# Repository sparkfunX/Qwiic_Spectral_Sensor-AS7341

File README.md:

# Qwiic_IR_Thermometer_MLX90614

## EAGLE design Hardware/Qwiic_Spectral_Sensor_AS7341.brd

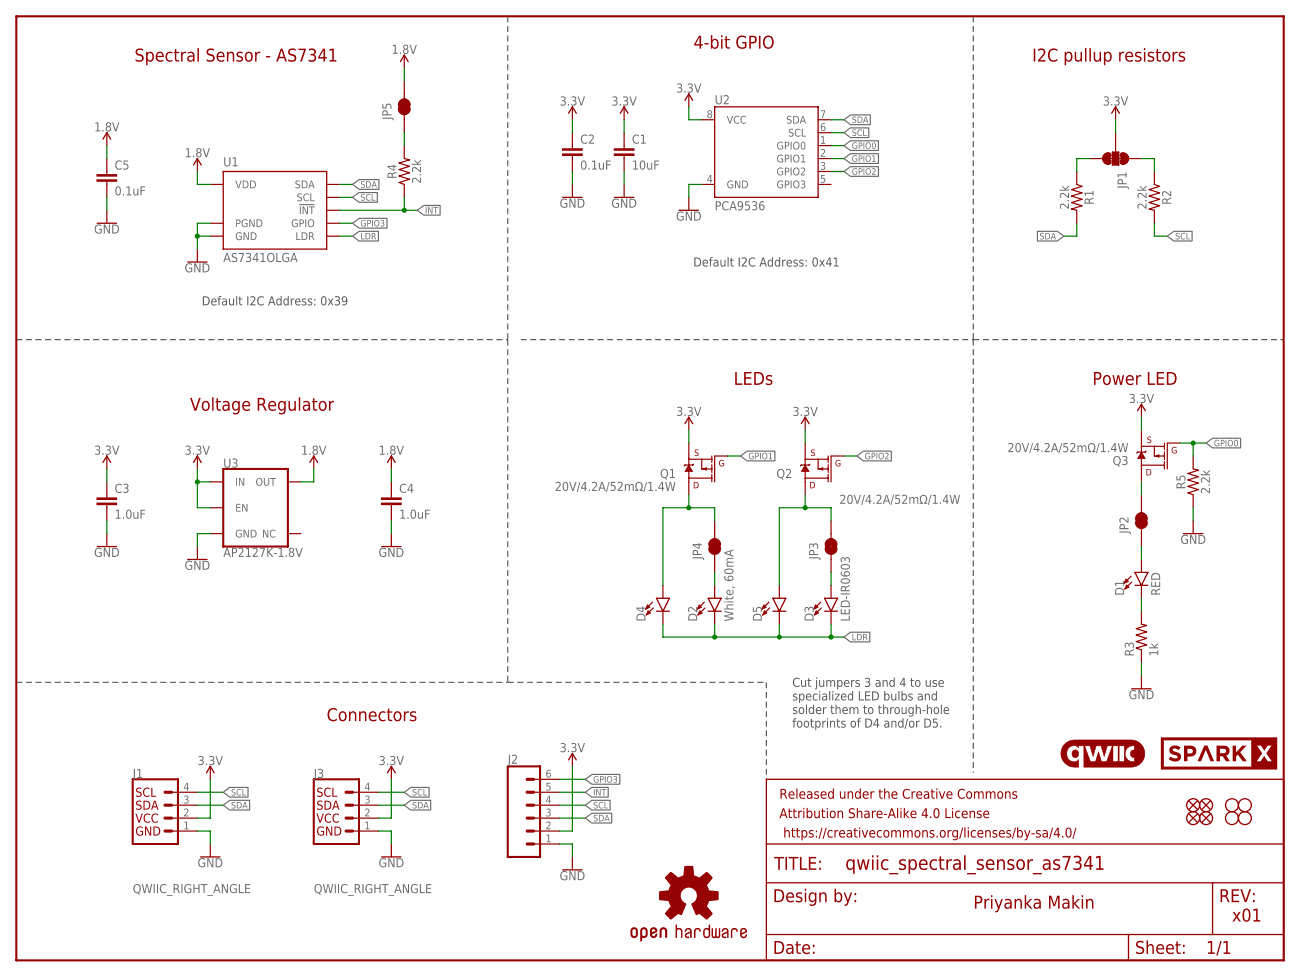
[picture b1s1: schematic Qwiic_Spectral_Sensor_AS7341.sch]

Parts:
C1: 10uF; 0603
C2, C5: 0.1uF; 0603
C3, C4: 1.0uF; 0603
D1: RED; LED-0603
D2: White, 60mA; SUPER_BRIGHT_SMD_LED_3014
D3: LED-IR0603; LED-0603
D4, D5: LED-3MM-NO_SILK; LED_3MM-NS
FD1, FD2, FD3, FD4: FIDUCIAL1X2; FIDUCIAL-1X2
FRAME1: FRAME-LETTER; CREATIVE_COMMONS
H1, H2, H3, H4: STAND-OFF
J1, J3: QWIIC_RIGHT_ANGLE; JST04_1MM_RA
J2: CONN_06NO_SILK_FEMALE_PTH; 1X06_NO_SILK
JP1: JUMPER-SMT_3_2-NC_TRACE_SILK; SMT-JUMPER_3_2-NC_TRACE_SILK
JP2, JP3, JP4, JP5: JUMPER-SMT_2_NC_TRACE_SILK; SMT-JUMPER_2_NC_TRACE_SILK
LOGO1: QWIIC_LOGO_6MM; QWIIC_6MM
Q1, Q2, Q3: 20V/4.2A/52mΩ/1.4W; SOT23-3
R1, R2, R4, R5: 2.2k; 0603
R3: 1k; 0603
U1: AS7341OLGA; OLGA8
U2: PCA9536; MSOP8
U3: AP2127K-1.8V; SOT23-5
U$1: OSHW-LOGOS; OSHW-LOGO-S
U$31: SPARKX-LOGO3; SPARKX-SMALL

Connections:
1.8V: C4.1, C5.1, JP5.2, U1.1 (VDD), U3.5 (OUT)
3.3V: C1.1, C2.1, C3.1, J1.2, J2.2, J3.2, JP1.2, Q1.2 (S), Q2.2 (S), Q3.2 (S), U2.8 (VCC), U3.1 (IN), U3.3 (EN)
!INT!: J2.5, R4.1, U1.7 (!INT!)
GND: C1.2, C2.2, C3.2, C4.2, C5.2, J1.1, J2.1, J3.1, R3.1, R5.1, U1.3 (GND), U1.5 (PGND), U2.4 (GND), U3.2 (GND)
GPIO0: Q3.1 (G), R5.2, U2.1 (GPIO0)
GPIO1: Q1.1 (G), U2.2 (GPIO1)
GPIO2: Q2.1 (G), U2.3 (GPIO2)
GPIO3: J2.6, U1.6 (GPIO)
LDR: D2.C, D3.C, D4.K (C), D5.K (C), U1.4 (LDR)
unnamed: JP1.3, R1.1
unnamed: D1.C, R3.2
unnamed: JP1.1, R2.1
unnamed: D1.A, JP2.1
unnamed: D2.A, JP4.1
unnamed: JP2.2, Q3.3 (D)
unnamed: D3.A, JP3.1
unnamed: D4.A, JP4.2, Q1.3 (D)
unnamed: D5.A, JP3.2, Q2.3 (D)
unnamed: JP5.1, R4.2
SCL: J1.4, J2.4, J3.4, R2.2, U1.2 (SCL), U2.6 (SCL)
SDA: J1.3, J2.3, J3.3, R1.2, U1.8 (SDA), U2.7 (SDA)

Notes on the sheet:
x01
Priyanka Makin
Connectors
Spectral Sensor - AS7341
4-bit GPIO
Power LED
Default I2C Address: 0x39
Default I2C Address: 0x41
I2C pullup resistors
Voltage Regulator
LEDs
Cut jumpers 3 and 4 to use specialized LED bulbs and solder them to through-hole footprints of D4 and/or D5.

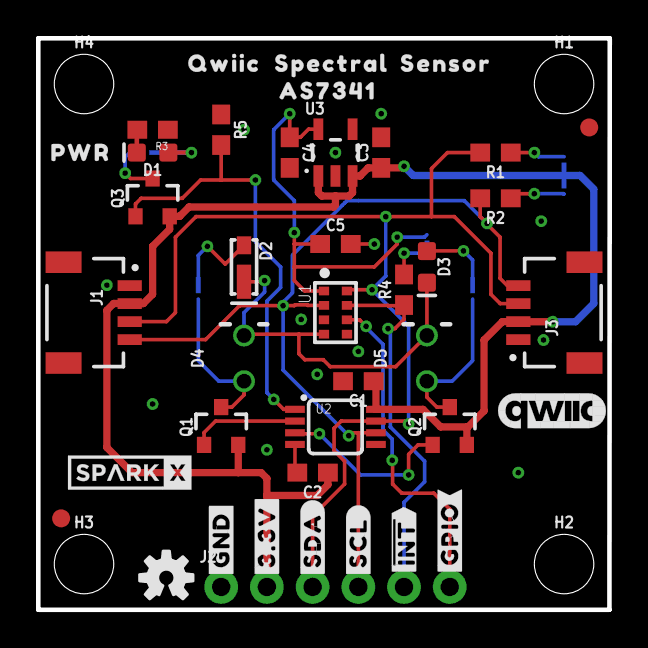
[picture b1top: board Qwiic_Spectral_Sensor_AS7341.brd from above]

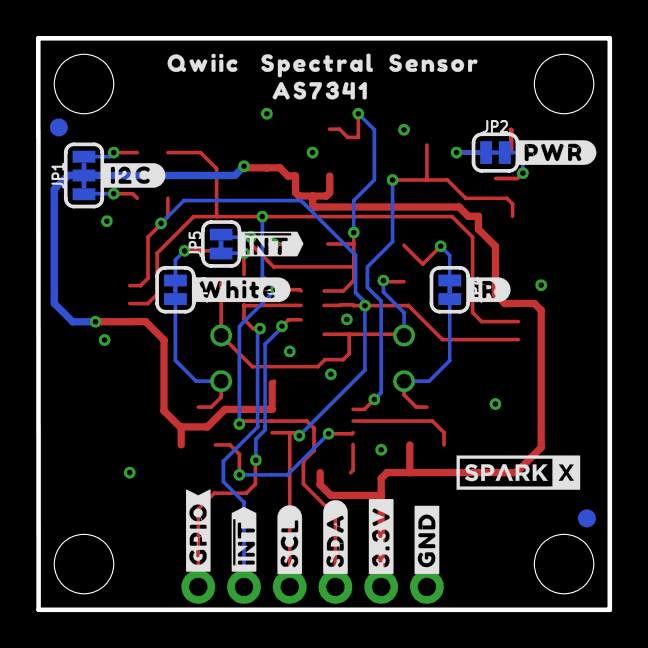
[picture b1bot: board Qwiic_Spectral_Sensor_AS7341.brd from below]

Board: 2 copper layers, 31.8 x 31.8 mm, 68 parts (23 on the bottom side), 21 nets.

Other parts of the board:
U$3, U$4: QWIIC0
U$5, U$8: SPECTRAL0
U$7: SPARKX-SMALL
U$9: #I2C#0
U$10: #PWR#0
U$11, U$21: SENSOR0
U$12: PWR0
U$13, U$14: #GND#0
U$15, U$16: #3#3V#0
U$17, U$18: #SDA#0
U$19, U$20: #SCL#0
U$22, U$23: AS73410
U$24, U$25, U$30: ##INT##0
U$26, U$27: #GPIO#0
U$28: #IR#0
U$29: #WHITE#0

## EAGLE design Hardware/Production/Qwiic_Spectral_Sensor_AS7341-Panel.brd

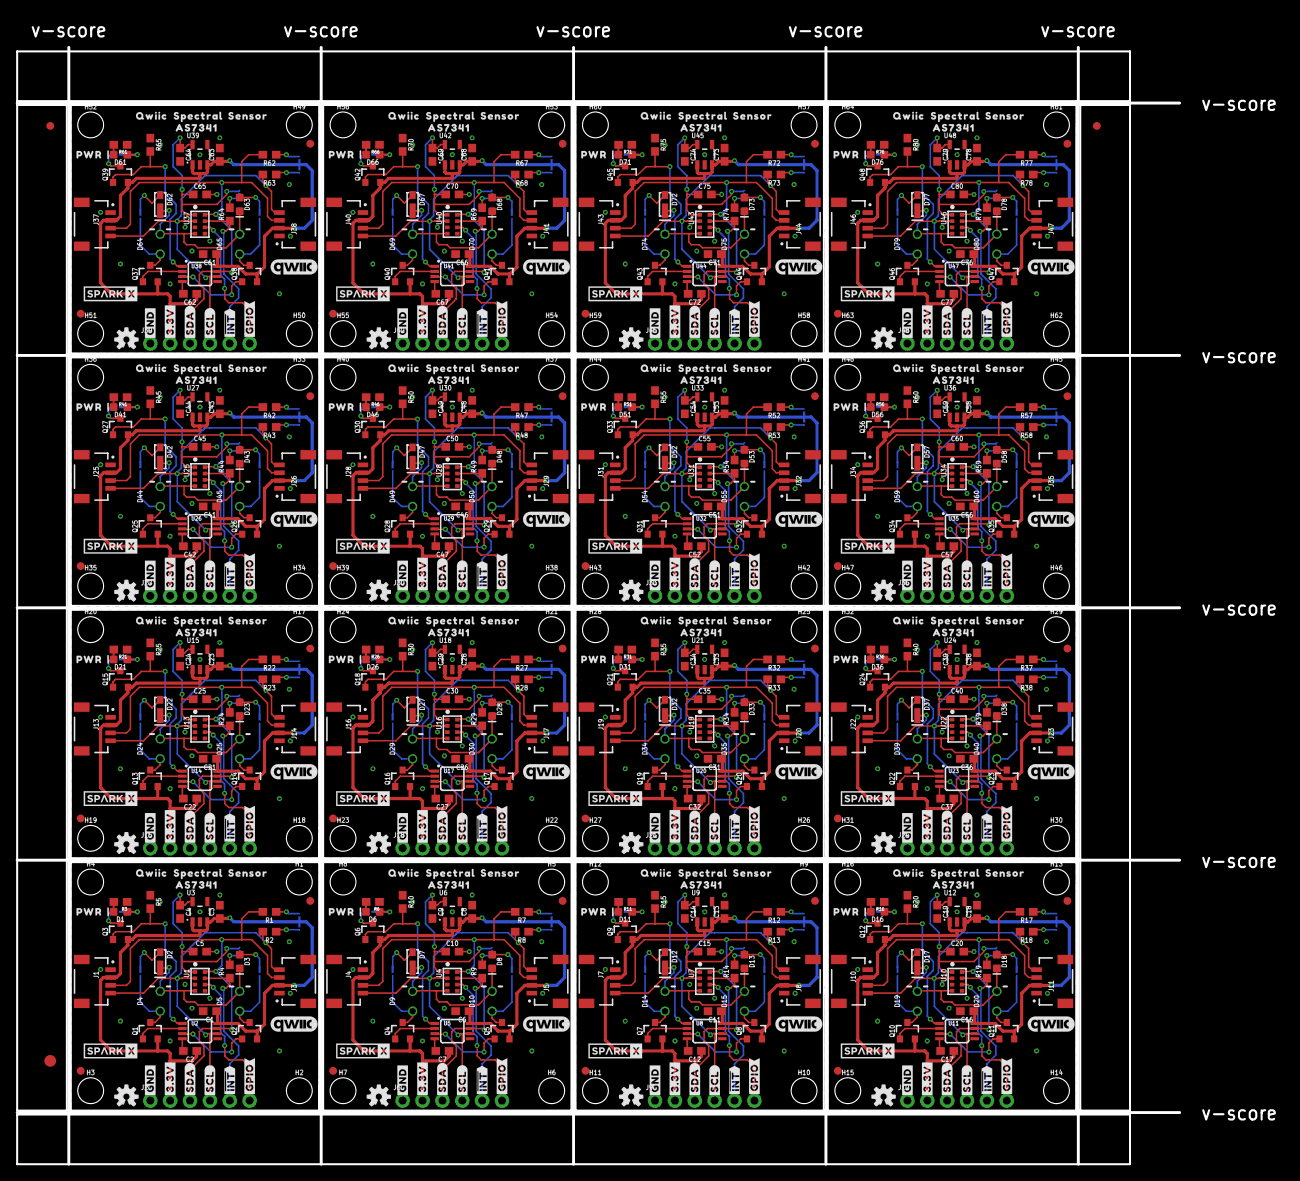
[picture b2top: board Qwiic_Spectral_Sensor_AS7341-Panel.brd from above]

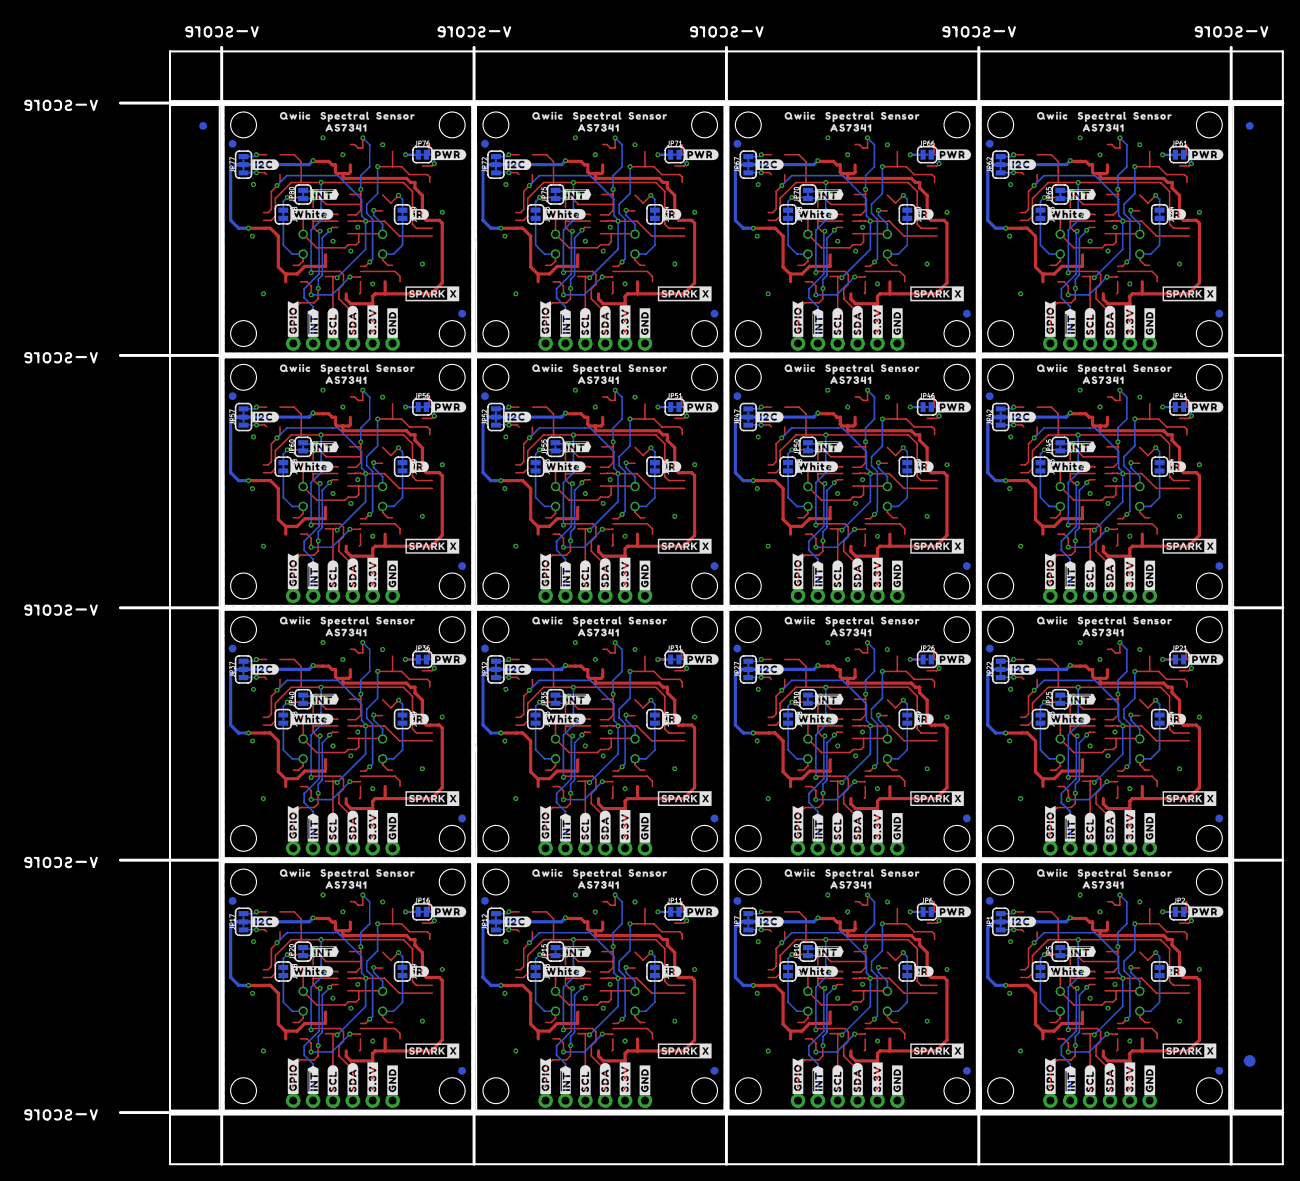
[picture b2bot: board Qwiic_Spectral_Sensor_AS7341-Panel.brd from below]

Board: 2 copper layers, 161.8 x 146.6 mm, 1078 parts (371 on the bottom side), 336 nets.

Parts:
C1, C6, C11, C16, C21, C26, C31, C36, C41, C46, C51, C56, C61, C66, C71, C76: 10uF; 0603
C2, C5, C7, C10, C12, C15, C17, C20, C22, C25, C27, C30, C32, C35, C37, C40, C42, C45, C47, C50, C52, C55, C57, C60, C62, C65, C67, C70, C72, C75, C77, C80: 0.1uF; 0603
C3, C4, C8, C9, C13, C14, C18, C19, C23, C24, C28, C29, C33, C34, C38, C39, C43, C44, C48, C49, C53, C54, C58, C59, C63, C64, C68, C69, C73, C74, C78, C79: 1.0uF; 0603
D1, D6, D11, D16, D21, D26, D31, D36, D41, D46, D51, D56, D61, D66, D71, D76: RED; LED-0603
D2, D7, D12, D17, D22, D27, D32, D37, D42, D47, D52, D57, D62, D67, D72, D77: White, 60mA; SUPER_BRIGHT_SMD_LED_3014
D3, D8, D13, D18, D23, D28, D33, D38, D43, D48, D53, D58, D63, D68, D73, D78: LED-IR0603; LED-0603
D4, D5, D9, D10, D14, D15, D19, D20, D24, D25, D29, D30, D34, D35, D39, D40, D44, D45, D49, D50, D54, D55, D59, D60, D64, D65, D69, D70, D74, D75, D79, D80: LED_3MM-NS
E$1, E$2, E$3, E$4: FIDUCIAL-1X2
E$5, E$6: FIDUCIAL-1.5X3
FD1, FD2, FD3, FD4, FD5, FD6, FD7, FD8, FD9, FD10, FD11, FD12, FD13, FD14, FD15, FD16, FD17, FD18, FD19, FD20, FD21, FD22, FD23, FD24, FD25, FD26, FD27, FD28, FD29, FD30, FD31, FD32, FD33, FD34, FD35, FD36, FD37, FD38, FD39, FD40, FD41, FD42, FD43, FD44, FD45, FD46, FD47, FD48, FD49, FD50, FD51, FD52, FD53, FD54, FD55, FD56, FD57, FD58, FD59, FD60, FD61, FD62, FD63, FD64: FIDUCIAL1X2; FIDUCIAL-1X2
H1, H2, H3, H4, H5, H6, H7, H8, H9, H10, H11, H12, H13, H14, H15, H16, H17, H18, H19, H20, H21, H22, H23, H24, H25, H26, H27, H28, H29, H30, H31, H32, H33, H34, H35, H36, H37, H38, H39, H40, H41, H42, H43, H44, H45, H46, H47, H48, H49, H50, H51, H52, H53, H54, H55, H56, H57, H58, H59, H60, H61, H62, H63, H64: STAND-OFF
J1, J3, J4, J5, J7, J8, J10, J11, J13, J14, J16, J17, J19, J20, J22, J23, J25, J26, J28, J29, J31, J32, J34, J35, J37, J38, J40, J41, J43, J44, J46, J47: QWIIC_RIGHT_ANGLE; JST04_1MM_RA
J2, J6, J9, J12, J15, J18, J21, J24, J27, J30, J33, J36, J39, J42, J45, J48: 1X06_NO_SILK
JP1, JP7, JP12, JP17, JP22, JP27, JP32, JP37, JP42, JP47, JP52, JP57, JP62, JP67, JP72, JP77: JUMPER-SMT_3_2-NC_TRACE_SILK; SMT-JUMPER_3_2-NC_TRACE_SILK
JP2, JP3, JP4, JP5, JP6, JP8, JP9, JP10, JP11, JP13, JP14, JP15, JP16, JP18, JP19, JP20, JP21, JP23, JP24, JP25, JP26, JP28, JP29, JP30, JP31, JP33, JP34, JP35, JP36, JP38, JP39, JP40, JP41, JP43, JP44, JP45, JP46, JP48, JP49, JP50, JP51, JP53, JP54, JP55, JP56, JP58, JP59, JP60, JP61, JP63, JP64, JP65, JP66, JP68, JP69, JP70, JP71, JP73, JP74, JP75, JP76, JP78, JP79, JP80: JUMPER-SMT_2_NC_TRACE_SILK; SMT-JUMPER_2_NC_TRACE_SILK
Q1, Q2, Q3, Q4, Q5, Q6, Q7, Q8, Q9, Q10, Q11, Q12, Q13, Q14, Q15, Q16, Q17, Q18, Q19, Q20, Q21, Q22, Q23, Q24, Q25, Q26, Q27, Q28, Q29, Q30, Q31, Q32, Q33, Q34, Q35, Q36, Q37, Q38, Q39, Q40, Q41, Q42, Q43, Q44, Q45, Q46, Q47, Q48: 20V/4.2A/52mΩ/1.4W; SOT23-3
R1, R2, R4, R5, R7, R8, R9, R10, R12, R13, R14, R15, R17, R18, R19, R20, R22, R23, R24, R25, R27, R28, R29, R30, R32, R33, R34, R35, R37, R38, R39, R40, R42, R43, R44, R45, R47, R48, R49, R50, R52, R53, R54, R55, R57, R58, R59, R60, R62, R63, R64, R65, R67, R68, R69, R70, R72, R73, R74, R75, R77, R78, R79, R80: 2.2k; 0603
R3, R6, R11, R16, R21, R26, R31, R36, R41, R46, R51, R56, R61, R66, R71, R76: 1k; 0603
U1, U4, U7, U10, U13, U16, U19, U22, U25, U28, U31, U34, U37, U40, U43, U46: AS7341OLGA; OLGA8
U2, U5, U8, U11, U14, U17, U20, U23, U26, U29, U32, U35, U38, U41, U44, U47: PCA9536; MSOP8
U3, U6, U9, U12, U15, U18, U21, U24, U27, U30, U33, U36, U39, U42, U45, U48: AP2127K-1.8V; SOT23-5
U$1, U$31, U$61, U$91, U$121, U$151, U$181, U$211, U$241, U$271, U$301, U$331, U$361, U$391, U$421, U$451: OSHW-LOGOS; OSHW-LOGO-S
U$2, U$32, U$62, U$92, U$122, U$152, U$182, U$212, U$242, U$272, U$302, U$332, U$362, U$392, U$422, U$452: QWIIC_6MM
U$3, U$4, U$46, U$47, U$76, U$77, U$106, U$107, U$136, U$137, U$166, U$167, U$196, U$197, U$226, U$227, U$256, U$257, U$286, U$287, U$316, U$317, U$346, U$347, U$376, U$377, U$406, U$407, U$436, U$437, U$466, U$467: QWIIC0
U$5, U$8, U$48, U$49, U$78, U$79, U$108, U$109, U$138, U$139, U$168, U$169, U$198, U$199, U$228, U$229, U$258, U$259, U$288, U$289, U$318, U$319, U$348, U$349, U$378, U$379, U$408, U$409, U$438, U$439, U$468, U$469: SPECTRAL0
U$6, U$7, U$44, U$45, U$74, U$75, U$104, U$105, U$134, U$135, U$164, U$165, U$194, U$195, U$224, U$225, U$254, U$255, U$284, U$285, U$314, U$315, U$344, U$345, U$374, U$375, U$404, U$405, U$434, U$435, U$464, U$465: SPARKX-SMALL
U$9, U$35, U$65, U$95, U$125, U$155, U$185, U$215, U$245, U$275, U$305, U$335, U$365, U$395, U$425, U$455: #I2C#0
U$10, U$34, U$64, U$94, U$124, U$154, U$184, U$214, U$244, U$274, U$304, U$334, U$364, U$394, U$424, U$454: #PWR#0
U$11, U$21, U$50, U$51, U$80, U$81, U$110, U$111, U$140, U$141, U$170, U$171, U$200, U$201, U$230, U$231, U$260, U$261, U$290, U$291, U$320, U$321, U$350, U$351, U$380, U$381, U$410, U$411, U$440, U$441, U$470, U$471: SENSOR0
U$12, U$33, U$63, U$93, U$123, U$153, U$183, U$213, U$243, U$273, U$303, U$333, U$363, U$393, U$423, U$453: PWR0
U$13, U$14, U$36, U$37, U$66, U$67, U$96, U$97, U$126, U$127, U$156, U$157, U$186, U$187, U$216, U$217, U$246, U$247, U$276, U$277, U$306, U$307, U$336, U$337, U$366, U$367, U$396, U$397, U$426, U$427, U$456, U$457: #GND#0
U$15, U$16, U$38, U$39, U$68, U$69, U$98, U$99, U$128, U$129, U$158, U$159, U$188, U$189, U$218, U$219, U$248, U$249, U$278, U$279, U$308, U$309, U$338, U$339, U$368, U$369, U$398, U$399, U$428, U$429, U$458, U$459: #3#3V#0
U$17, U$18, U$40, U$41, U$70, U$71, U$100, U$101, U$130, U$131, U$160, U$161, U$190, U$191, U$220, U$221, U$250, U$251, U$280, U$281, U$310, U$311, U$340, U$341, U$370, U$371, U$400, U$401, U$430, U$431, U$460, U$461: #SDA#0
U$19, U$20, U$42, U$43, U$72, U$73, U$102, U$103, U$132, U$133, U$162, U$163, U$192, U$193, U$222, U$223, U$252, U$253, U$282, U$283, U$312, U$313, U$342, U$343, U$372, U$373, U$402, U$403, U$432, U$433, U$462, U$463: #SCL#0
U$22, U$23, U$52, U$53, U$82, U$83, U$112, U$113, U$142, U$143, U$172, U$173, U$202, U$203, U$232, U$233, U$262, U$263, U$292, U$293, U$322, U$323, U$352, U$353, U$382, U$383, U$412, U$413, U$442, U$443, U$472, U$473: AS73410
U$24, U$25, U$30, U$56, U$57, U$58, U$86, U$87, U$88, U$116, U$117, U$118, U$146, U$147, U$148, U$176, U$177, U$178, U$206, U$207, U$208, U$236, U$237, U$238, U$266, U$267, U$268, U$296, U$297, U$298, U$326, U$327, U$328, U$356, U$357, U$358, U$386, U$387, U$388, U$416, U$417, U$418, U$446, U$447, U$448, U$476, U$477, U$478: ##INT##0
U$26, U$27, U$59, U$60, U$89, U$90, U$119, U$120, U$149, U$150, U$179, U$180, U$209, U$210, U$239, U$240, U$269, U$270, U$299, U$300, U$329, U$330, U$359, U$360, U$389, U$390, U$419, U$420, U$449, U$450, U$479, U$480: #GPIO#0
U$28, U$54, U$84, U$114, U$144, U$174, U$204, U$234, U$264, U$294, U$324, U$354, U$384, U$414, U$444, U$474: #IR#0
U$29, U$55, U$85, U$115, U$145, U$175, U$205, U$235, U$265, U$295, U$325, U$355, U$385, U$415, U$445, U$475: #WHITE#0

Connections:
1.8V: C4.1, C5.1, JP5.2, U1.1, U3.5
1.8V1: C9.1, C10.1, JP10.2, U4.1, U6.5
1.8V2: C14.1, C15.1, JP15.2, U7.1, U9.5
1.8V3: C19.1, C20.1, JP20.2, U10.1, U12.5
1.8V4: C24.1, C25.1, JP25.2, U13.1, U15.5
1.8V5: C29.1, C30.1, JP30.2, U16.1, U18.5
1.8V6: C34.1, C35.1, JP35.2, U19.1, U21.5
1.8V7: C39.1, C40.1, JP40.2, U22.1, U24.5
1.8V8: C44.1, C45.1, JP45.2, U25.1, U27.5
1.8V9: C49.1, C50.1, JP50.2, U28.1, U30.5
1.8V10: C54.1, C55.1, JP55.2, U31.1, U33.5
1.8V11: C59.1, C60.1, JP60.2, U34.1, U36.5
1.8V12: C64.1, C65.1, JP65.2, U37.1, U39.5
1.8V13: C69.1, C70.1, JP70.2, U40.1, U42.5
1.8V14: C74.1, C75.1, JP75.2, U43.1, U45.5
1.8V15: C79.1, C80.1, JP80.2, U46.1, U48.5
3.3V: C1.1, C2.1, C3.1, J1.2, J2.2, J3.2, JP1.2, Q1.2, Q2.2, Q3.2, U2.8, U3.1, U3.3
3.3V1: C6.1, C7.1, C8.1, J4.2, J5.2, J6.2, JP7.2, Q4.2, Q5.2, Q6.2, U5.8, U6.1, U6.3
3.3V2: C11.1, C12.1, C13.1, J7.2, J8.2, J9.2, JP12.2, Q7.2, Q8.2, Q9.2, U8.8, U9.1, U9.3
3.3V3: C16.1, C17.1, C18.1, J10.2, J11.2, J12.2, JP17.2, Q10.2, Q11.2, Q12.2, U11.8, U12.1, U12.3
3.3V4: C21.1, C22.1, C23.1, J13.2, J14.2, J15.2, JP22.2, Q13.2, Q14.2, Q15.2, U14.8, U15.1, U15.3
3.3V5: C26.1, C27.1, C28.1, J16.2, J17.2, J18.2, JP27.2, Q16.2, Q17.2, Q18.2, U17.8, U18.1, U18.3
3.3V6: C31.1, C32.1, C33.1, J19.2, J20.2, J21.2, JP32.2, Q19.2, Q20.2, Q21.2, U20.8, U21.1, U21.3
3.3V7: C36.1, C37.1, C38.1, J22.2, J23.2, J24.2, JP37.2, Q22.2, Q23.2, Q24.2, U23.8, U24.1, U24.3
3.3V8: C41.1, C42.1, C43.1, J25.2, J26.2, J27.2, JP42.2, Q25.2, Q26.2, Q27.2, U26.8, U27.1, U27.3
3.3V9: C46.1, C47.1, C48.1, J28.2, J29.2, J30.2, JP47.2, Q28.2, Q29.2, Q30.2, U29.8, U30.1, U30.3
3.3V10: C51.1, C52.1, C53.1, J31.2, J32.2, J33.2, JP52.2, Q31.2, Q32.2, Q33.2, U32.8, U33.1, U33.3
3.3V11: C56.1, C57.1, C58.1, J34.2, J35.2, J36.2, JP57.2, Q34.2, Q35.2, Q36.2, U35.8, U36.1, U36.3
3.3V12: C61.1, C62.1, C63.1, J37.2, J38.2, J39.2, JP62.2, Q37.2, Q38.2, Q39.2, U38.8, U39.1, U39.3
3.3V13: C66.1, C67.1, C68.1, J40.2, J41.2, J42.2, JP67.2, Q40.2, Q41.2, Q42.2, U41.8, U42.1, U42.3
3.3V14: C71.1, C72.1, C73.1, J43.2, J44.2, J45.2, JP72.2, Q43.2, Q44.2, Q45.2, U44.8, U45.1, U45.3
3.3V15: C76.1, C77.1, C78.1, J46.2, J47.2, J48.2, JP77.2, Q46.2, Q47.2, Q48.2, U47.8, U48.1, U48.3
!INT!: J2.5, R4.1, U1.7
!INT!1: J6.5, R9.1, U4.7
!INT!2: J9.5, R14.1, U7.7
!INT!3: J12.5, R19.1, U10.7
!INT!4: J15.5, R24.1, U13.7
!INT!5: J18.5, R29.1, U16.7
!INT!6: J21.5, R34.1, U19.7
!INT!7: J24.5, R39.1, U22.7
!INT!8: J27.5, R44.1, U25.7
!INT!9: J30.5, R49.1, U28.7
!INT!10: J33.5, R54.1, U31.7
!INT!11: J36.5, R59.1, U34.7
!INT!12: J39.5, R64.1, U37.7
!INT!13: J42.5, R69.1, U40.7
!INT!14: J45.5, R74.1, U43.7
!INT!15: J48.5, R79.1, U46.7
GND: C1.2, C2.2, C3.2, C4.2, C5.2, J1.1, J2.1, J3.1, R3.1, R5.1, U1.3, U1.5, U2.4, U3.2
GND1: C6.2, C7.2, C8.2, C9.2, C10.2, J4.1, J5.1, J6.1, R6.1, R10.1, U4.3, U4.5, U5.4, U6.2
GND2: C11.2, C12.2, C13.2, C14.2, C15.2, J7.1, J8.1, J9.1, R11.1, R15.1, U7.3, U7.5, U8.4, U9.2
GND3: C16.2, C17.2, C18.2, C19.2, C20.2, J10.1, J11.1, J12.1, R16.1, R20.1, U10.3, U10.5, U11.4, U12.2
GND4: C21.2, C22.2, C23.2, C24.2, C25.2, J13.1, J14.1, J15.1, R21.1, R25.1, U13.3, U13.5, U14.4, U15.2
GND5: C26.2, C27.2, C28.2, C29.2, C30.2, J16.1, J17.1, J18.1, R26.1, R30.1, U16.3, U16.5, U17.4, U18.2
GND6: C31.2, C32.2, C33.2, C34.2, C35.2, J19.1, J20.1, J21.1, R31.1, R35.1, U19.3, U19.5, U20.4, U21.2
GND7: C36.2, C37.2, C38.2, C39.2, C40.2, J22.1, J23.1, J24.1, R36.1, R40.1, U22.3, U22.5, U23.4, U24.2
GND8: C41.2, C42.2, C43.2, C44.2, C45.2, J25.1, J26.1, J27.1, R41.1, R45.1, U25.3, U25.5, U26.4, U27.2
GND9: C46.2, C47.2, C48.2, C49.2, C50.2, J28.1, J29.1, J30.1, R46.1, R50.1, U28.3, U28.5, U29.4, U30.2
GND10: C51.2, C52.2, C53.2, C54.2, C55.2, J31.1, J32.1, J33.1, R51.1, R55.1, U31.3, U31.5, U32.4, U33.2
GND11: C56.2, C57.2, C58.2, C59.2, C60.2, J34.1, J35.1, J36.1, R56.1, R60.1, U34.3, U34.5, U35.4, U36.2
GND12: C61.2, C62.2, C63.2, C64.2, C65.2, J37.1, J38.1, J39.1, R61.1, R65.1, U37.3, U37.5, U38.4, U39.2
GND13: C66.2, C67.2, C68.2, C69.2, C70.2, J40.1, J41.1, J42.1, R66.1, R70.1, U40.3, U40.5, U41.4, U42.2
GND14: C71.2, C72.2, C73.2, C74.2, C75.2, J43.1, J44.1, J45.1, R71.1, R75.1, U43.3, U43.5, U44.4, U45.2
GND15: C76.2, C77.2, C78.2, C79.2, C80.2, J46.1, J47.1, J48.1, R76.1, R80.1, U46.3, U46.5, U47.4, U48.2
GPIO0: Q3.1, R5.2, U2.1
GPIO1: Q1.1, U2.2
GPIO2: Q2.1, U2.3
GPIO3: J2.6, U1.6
GPIO4: Q6.1, R10.2, U5.1
GPIO5: Q4.1, U5.2
GPIO6: Q5.1, U5.3
GPIO7: J6.6, U4.6
GPIO8: Q9.1, R15.2, U8.1
GPIO9: Q7.1, U8.2
GPIO10: Q8.1, U8.3
GPIO11: J9.6, U7.6
GPIO12: Q12.1, R20.2, U11.1
GPIO13: Q10.1, U11.2
GPIO14: Q11.1, U11.3
GPIO15: J12.6, U10.6
GPIO16: Q15.1, R25.2, U14.1
GPIO17: Q13.1, U14.2
GPIO18: Q14.1, U14.3
GPIO19: J15.6, U13.6
GPIO20: Q18.1, R30.2, U17.1
GPIO21: Q16.1, U17.2
GPIO22: Q17.1, U17.3
GPIO23: J18.6, U16.6
GPIO24: Q21.1, R35.2, U20.1
GPIO25: Q19.1, U20.2
GPIO26: Q20.1, U20.3
GPIO27: J21.6, U19.6
GPIO28: Q24.1, R40.2, U23.1
GPIO29: Q22.1, U23.2
GPIO30: Q23.1, U23.3
GPIO31: J24.6, U22.6
GPIO32: Q27.1, R45.2, U26.1
GPIO33: Q25.1, U26.2
GPIO34: Q26.1, U26.3
GPIO35: J27.6, U25.6
GPIO36: Q30.1, R50.2, U29.1
GPIO37: Q28.1, U29.2
GPIO38: Q29.1, U29.3
GPIO39: J30.6, U28.6
GPIO40: Q33.1, R55.2, U32.1
GPIO41: Q31.1, U32.2
GPIO42: Q32.1, U32.3
GPIO43: J33.6, U31.6
GPIO44: Q36.1, R60.2, U35.1
GPIO45: Q34.1, U35.2
GPIO46: Q35.1, U35.3
GPIO47: J36.6, U34.6
GPIO48: Q39.1, R65.2, U38.1
GPIO49: Q37.1, U38.2
GPIO50: Q38.1, U38.3
GPIO51: J39.6, U37.6
GPIO52: Q42.1, R70.2, U41.1
GPIO53: Q40.1, U41.2
GPIO54: Q41.1, U41.3
GPIO55: J42.6, U40.6
GPIO56: Q45.1, R75.2, U44.1
GPIO57: Q43.1, U44.2
GPIO58: Q44.1, U44.3
GPIO59: J45.6, U43.6
GPIO60: Q48.1, R80.2, U47.1
GPIO61: Q46.1, U47.2
GPIO62: Q47.1, U47.3
GPIO63: J48.6, U46.6
LDR: D2.C, D3.C, D4.K, D5.K, U1.4
LDR1: D7.C, D8.C, D9.K, D10.K, U4.4
LDR2: D12.C, D13.C, D14.K, D15.K, U7.4
LDR3: D17.C, D18.C, D19.K, D20.K, U10.4
LDR4: D22.C, D23.C, D24.K, D25.K, U13.4
LDR5: D27.C, D28.C, D29.K, D30.K, U16.4
LDR6: D32.C, D33.C, D34.K, D35.K, U19.4
LDR7: D37.C, D38.C, D39.K, D40.K, U22.4
LDR8: D42.C, D43.C, D44.K, D45.K, U25.4
LDR9: D47.C, D48.C, D49.K, D50.K, U28.4
LDR10: D52.C, D53.C, D54.K, D55.K, U31.4
LDR11: D57.C, D58.C, D59.K, D60.K, U34.4
LDR12: D62.C, D63.C, D64.K, D65.K, U37.4
LDR13: D67.C, D68.C, D69.K, D70.K, U40.4
LDR14: D72.C, D73.C, D74.K, D75.K, U43.4
LDR15: D77.C, D78.C, D79.K, D80.K, U46.4
unnamed: JP1.3, R1.1
unnamed: D1.C, R3.2
unnamed: JP1.1, R2.1
unnamed: D1.A, JP2.1
unnamed: D2.A, JP4.1
unnamed: JP2.2, Q3.3
unnamed: D3.A, JP3.1
unnamed: D4.A, JP4.2, Q1.3
unnamed: D5.A, JP3.2, Q2.3
unnamed: JP5.1, R4.2
unnamed: D6.C, R6.2
unnamed: D6.A, JP6.1
unnamed: JP7.3, R7.1
unnamed: JP7.1, R8.1
unnamed: D7.A, JP9.1
unnamed: D8.A, JP8.1
unnamed: D9.A, JP9.2, Q4.3
unnamed: D10.A, JP8.2, Q5.3
unnamed: JP6.2, Q6.3
unnamed: JP10.1, R9.2
unnamed: D11.C, R11.2
unnamed: D11.A, JP11.1
unnamed: JP12.3, R12.1
unnamed: JP12.1, R13.1
unnamed: D12.A, JP14.1
unnamed: D13.A, JP13.1
unnamed: D14.A, JP14.2, Q7.3
unnamed: D15.A, JP13.2, Q8.3
unnamed: JP11.2, Q9.3
unnamed: JP15.1, R14.2
unnamed: D16.C, R16.2
unnamed: D16.A, JP16.1
unnamed: JP17.3, R17.1
unnamed: JP17.1, R18.1
unnamed: D17.A, JP19.1
unnamed: D18.A, JP18.1
unnamed: D19.A, JP19.2, Q10.3
unnamed: D20.A, JP18.2, Q11.3
unnamed: JP16.2, Q12.3
unnamed: JP20.1, R19.2
unnamed: D21.C, R21.2
unnamed: D21.A, JP21.1
unnamed: JP22.3, R22.1
unnamed: JP22.1, R23.1
unnamed: D22.A, JP24.1
unnamed: D23.A, JP23.1
unnamed: D24.A, JP24.2, Q13.3
unnamed: D25.A, JP23.2, Q14.3
unnamed: JP21.2, Q15.3
unnamed: JP25.1, R24.2
unnamed: D26.C, R26.2
unnamed: D26.A, JP26.1
unnamed: JP27.3, R27.1
unnamed: JP27.1, R28.1
unnamed: D27.A, JP29.1
unnamed: D28.A, JP28.1
unnamed: D29.A, JP29.2, Q16.3
unnamed: D30.A, JP28.2, Q17.3
unnamed: JP26.2, Q18.3
unnamed: JP30.1, R29.2
unnamed: D31.C, R31.2
unnamed: D31.A, JP31.1
unnamed: JP32.3, R32.1
unnamed: JP32.1, R33.1
unnamed: D32.A, JP34.1
unnamed: D33.A, JP33.1
unnamed: D34.A, JP34.2, Q19.3
unnamed: D35.A, JP33.2, Q20.3
unnamed: JP31.2, Q21.3
unnamed: JP35.1, R34.2
unnamed: D36.C, R36.2
unnamed: D36.A, JP36.1
unnamed: JP37.3, R37.1
unnamed: JP37.1, R38.1
unnamed: D37.A, JP39.1
unnamed: D38.A, JP38.1
unnamed: D39.A, JP39.2, Q22.3
unnamed: D40.A, JP38.2, Q23.3
unnamed: JP36.2, Q24.3
unnamed: JP40.1, R39.2
unnamed: D41.C, R41.2
unnamed: D41.A, JP41.1
unnamed: JP42.3, R42.1
unnamed: JP42.1, R43.1
unnamed: D42.A, JP44.1
unnamed: D43.A, JP43.1
unnamed: D44.A, JP44.2, Q25.3
unnamed: D45.A, JP43.2, Q26.3
unnamed: JP41.2, Q27.3
unnamed: JP45.1, R44.2
unnamed: D46.C, R46.2
unnamed: D46.A, JP46.1
unnamed: JP47.3, R47.1
unnamed: JP47.1, R48.1
unnamed: D47.A, JP49.1
unnamed: D48.A, JP48.1
unnamed: D49.A, JP49.2, Q28.3
unnamed: D50.A, JP48.2, Q29.3
unnamed: JP46.2, Q30.3
unnamed: JP50.1, R49.2
unnamed: D51.C, R51.2
unnamed: D51.A, JP51.1
unnamed: JP52.3, R52.1
unnamed: JP52.1, R53.1
unnamed: D52.A, JP54.1
unnamed: D53.A, JP53.1
unnamed: D54.A, JP54.2, Q31.3
unnamed: D55.A, JP53.2, Q32.3
unnamed: JP51.2, Q33.3
unnamed: JP55.1, R54.2
unnamed: D56.C, R56.2
unnamed: D56.A, JP56.1
unnamed: JP57.3, R57.1
unnamed: JP57.1, R58.1
unnamed: D57.A, JP59.1
unnamed: D58.A, JP58.1
unnamed: D59.A, JP59.2, Q34.3
unnamed: D60.A, JP58.2, Q35.3
unnamed: JP56.2, Q36.3
unnamed: JP60.1, R59.2
unnamed: D61.C, R61.2
unnamed: D61.A, JP61.1
unnamed: JP62.3, R62.1
unnamed: JP62.1, R63.1
unnamed: D62.A, JP64.1
unnamed: D63.A, JP63.1
unnamed: D64.A, JP64.2, Q37.3
unnamed: D65.A, JP63.2, Q38.3
unnamed: JP61.2, Q39.3
unnamed: JP65.1, R64.2
unnamed: D66.C, R66.2
unnamed: D66.A, JP66.1
unnamed: JP67.3, R67.1
unnamed: JP67.1, R68.1
unnamed: D67.A, JP69.1
unnamed: D68.A, JP68.1
unnamed: D69.A, JP69.2, Q40.3
unnamed: D70.A, JP68.2, Q41.3
unnamed: JP66.2, Q42.3
unnamed: JP70.1, R69.2
unnamed: D71.C, R71.2
unnamed: D71.A, JP71.1
unnamed: JP72.3, R72.1
unnamed: JP72.1, R73.1
unnamed: D72.A, JP74.1
unnamed: D73.A, JP73.1
unnamed: D74.A, JP74.2, Q43.3
unnamed: D75.A, JP73.2, Q44.3
unnamed: JP71.2, Q45.3
unnamed: JP75.1, R74.2
unnamed: D76.C, R76.2
unnamed: D76.A, JP76.1
unnamed: JP77.3, R77.1
unnamed: JP77.1, R78.1
unnamed: D77.A, JP79.1
unnamed: D78.A, JP78.1
unnamed: D79.A, JP79.2, Q46.3
unnamed: D80.A, JP78.2, Q47.3
unnamed: JP76.2, Q48.3
unnamed: JP80.1, R79.2
SCL: J1.4, J2.4, J3.4, R2.2, U1.2, U2.6
SCL1: J4.4, J5.4, J6.4, R8.2, U4.2, U5.6
SCL2: J7.4, J8.4, J9.4, R13.2, U7.2, U8.6
SCL3: J10.4, J11.4, J12.4, R18.2, U10.2, U11.6
SCL4: J13.4, J14.4, J15.4, R23.2, U13.2, U14.6
SCL5: J16.4, J17.4, J18.4, R28.2, U16.2, U17.6
SCL6: J19.4, J20.4, J21.4, R33.2, U19.2, U20.6
SCL7: J22.4, J23.4, J24.4, R38.2, U22.2, U23.6
SCL8: J25.4, J26.4, J27.4, R43.2, U25.2, U26.6
SCL9: J28.4, J29.4, J30.4, R48.2, U28.2, U29.6
SCL10: J31.4, J32.4, J33.4, R53.2, U31.2, U32.6
SCL11: J34.4, J35.4, J36.4, R58.2, U34.2, U35.6
SCL12: J37.4, J38.4, J39.4, R63.2, U37.2, U38.6
SCL13: J40.4, J41.4, J42.4, R68.2, U40.2, U41.6
SCL14: J43.4, J44.4, J45.4, R73.2, U43.2, U44.6
SCL15: J46.4, J47.4, J48.4, R78.2, U46.2, U47.6
SDA: J1.3, J2.3, J3.3, R1.2, U1.8, U2.7
SDA1: J4.3, J5.3, J6.3, R7.2, U4.8, U5.7
SDA2: J7.3, J8.3, J9.3, R12.2, U7.8, U8.7
SDA3: J10.3, J11.3, J12.3, R17.2, U10.8, U11.7
SDA4: J13.3, J14.3, J15.3, R22.2, U13.8, U14.7
SDA5: J16.3, J17.3, J18.3, R27.2, U16.8, U17.7
SDA6: J19.3, J20.3, J21.3, R32.2, U19.8, U20.7
SDA7: J22.3, J23.3, J24.3, R37.2, U22.8, U23.7
SDA8: J25.3, J26.3, J27.3, R42.2, U25.8, U26.7
SDA9: J28.3, J29.3, J30.3, R47.2, U28.8, U29.7
SDA10: J31.3, J32.3, J33.3, R52.2, U31.8, U32.7
SDA11: J34.3, J35.3, J36.3, R57.2, U34.8, U35.7
SDA12: J37.3, J38.3, J39.3, R62.2, U37.8, U38.7
SDA13: J40.3, J41.3, J42.3, R67.2, U40.8, U41.7
SDA14: J43.3, J44.3, J45.3, R72.2, U43.8, U44.7
SDA15: J46.3, J47.3, J48.3, R77.2, U46.8, U47.7

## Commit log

2020-11-19 Initial commit
    Getting files in place
2020-11-19 Rename files. Actually using the AS7341
2020-11-19 Working on schematic
2020-11-20 First draft of schematic finished
2020-11-20 Added int pin to schematic
2020-11-20 added as7341 decoupling cap
2020-11-23 Board design
2020-11-23 Buzzard labels
2020-11-24 Board review notes
2020-11-24 Panelization
2021-01-19 Add schematic.
2021-01-19 Remove old files
2021-03-15 Added datasheets and application notes; added basic library and sketches examples.
2021-03-17 Added GPIO and interrupt sketches and library functions.
2021-03-21 Added Single channel measurement; fixed readAllChannel function; updated project per Nathan's suggestions
2021-03-22 Added Threshold Interrupt and Register Read/Write examples and corresponding library functions.

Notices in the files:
parts and their libraries:
SparkFun-Jumpers: Licensing: Creative Commons ShareAlike 4.0 International - https://creativecommons.org/licenses/by-sa/4.0
SparkFun-Aesthetics: Released under the Creative Commons Attribution Share-Alike 4.0 License
SparkFun-Aesthetics: https://creativecommons.org/licenses/by-sa/4.0
